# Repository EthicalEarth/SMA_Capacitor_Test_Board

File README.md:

# SMA_Capacitor_Test_Board
This test board you can use to test impedance and Q Factor with VNA

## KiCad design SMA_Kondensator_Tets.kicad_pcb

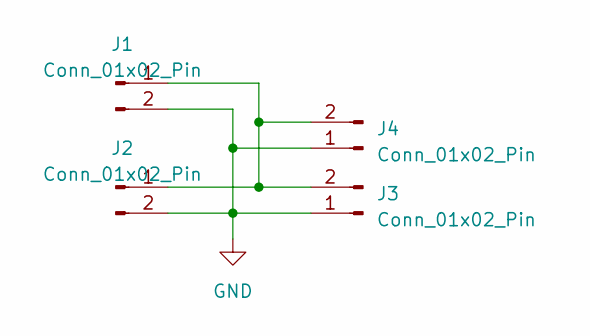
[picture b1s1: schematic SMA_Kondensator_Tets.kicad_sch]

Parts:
J1, J2: Conn_01x02_Pin; SMA_Amphenol_901-143_Horizontal
J3: Conn_01x02_Pin; L_1206_3216Metric
J4: Conn_01x02_Pin; Molex_Mini-Fit_Jr_5566-02A_2x01_P4.20mm_Vertical

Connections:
GND: J1.2, J2.2, J3.1, J4.1
unnamed: J1.1, J2.1, J3.2, J4.2

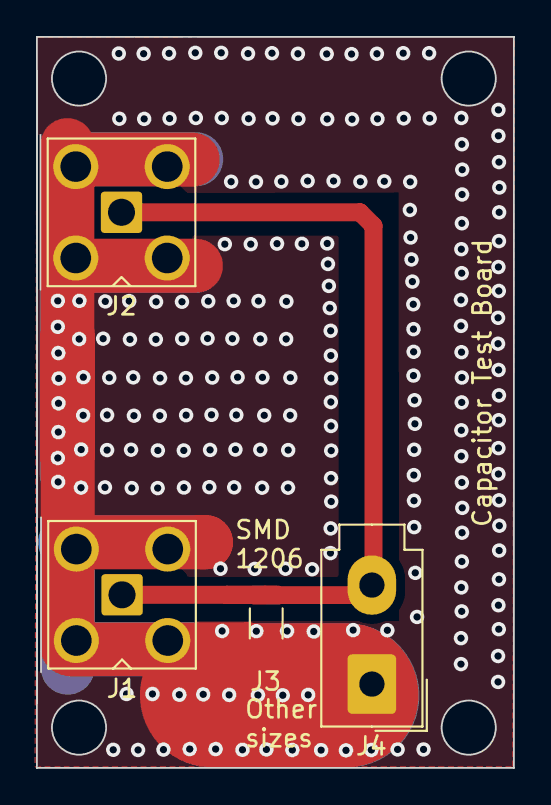
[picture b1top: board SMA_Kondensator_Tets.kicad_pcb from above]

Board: 2 copper layers, 26.5 x 40.6 mm, 4 parts (0 on the bottom side), 2 nets.

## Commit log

2023-11-05 Init
